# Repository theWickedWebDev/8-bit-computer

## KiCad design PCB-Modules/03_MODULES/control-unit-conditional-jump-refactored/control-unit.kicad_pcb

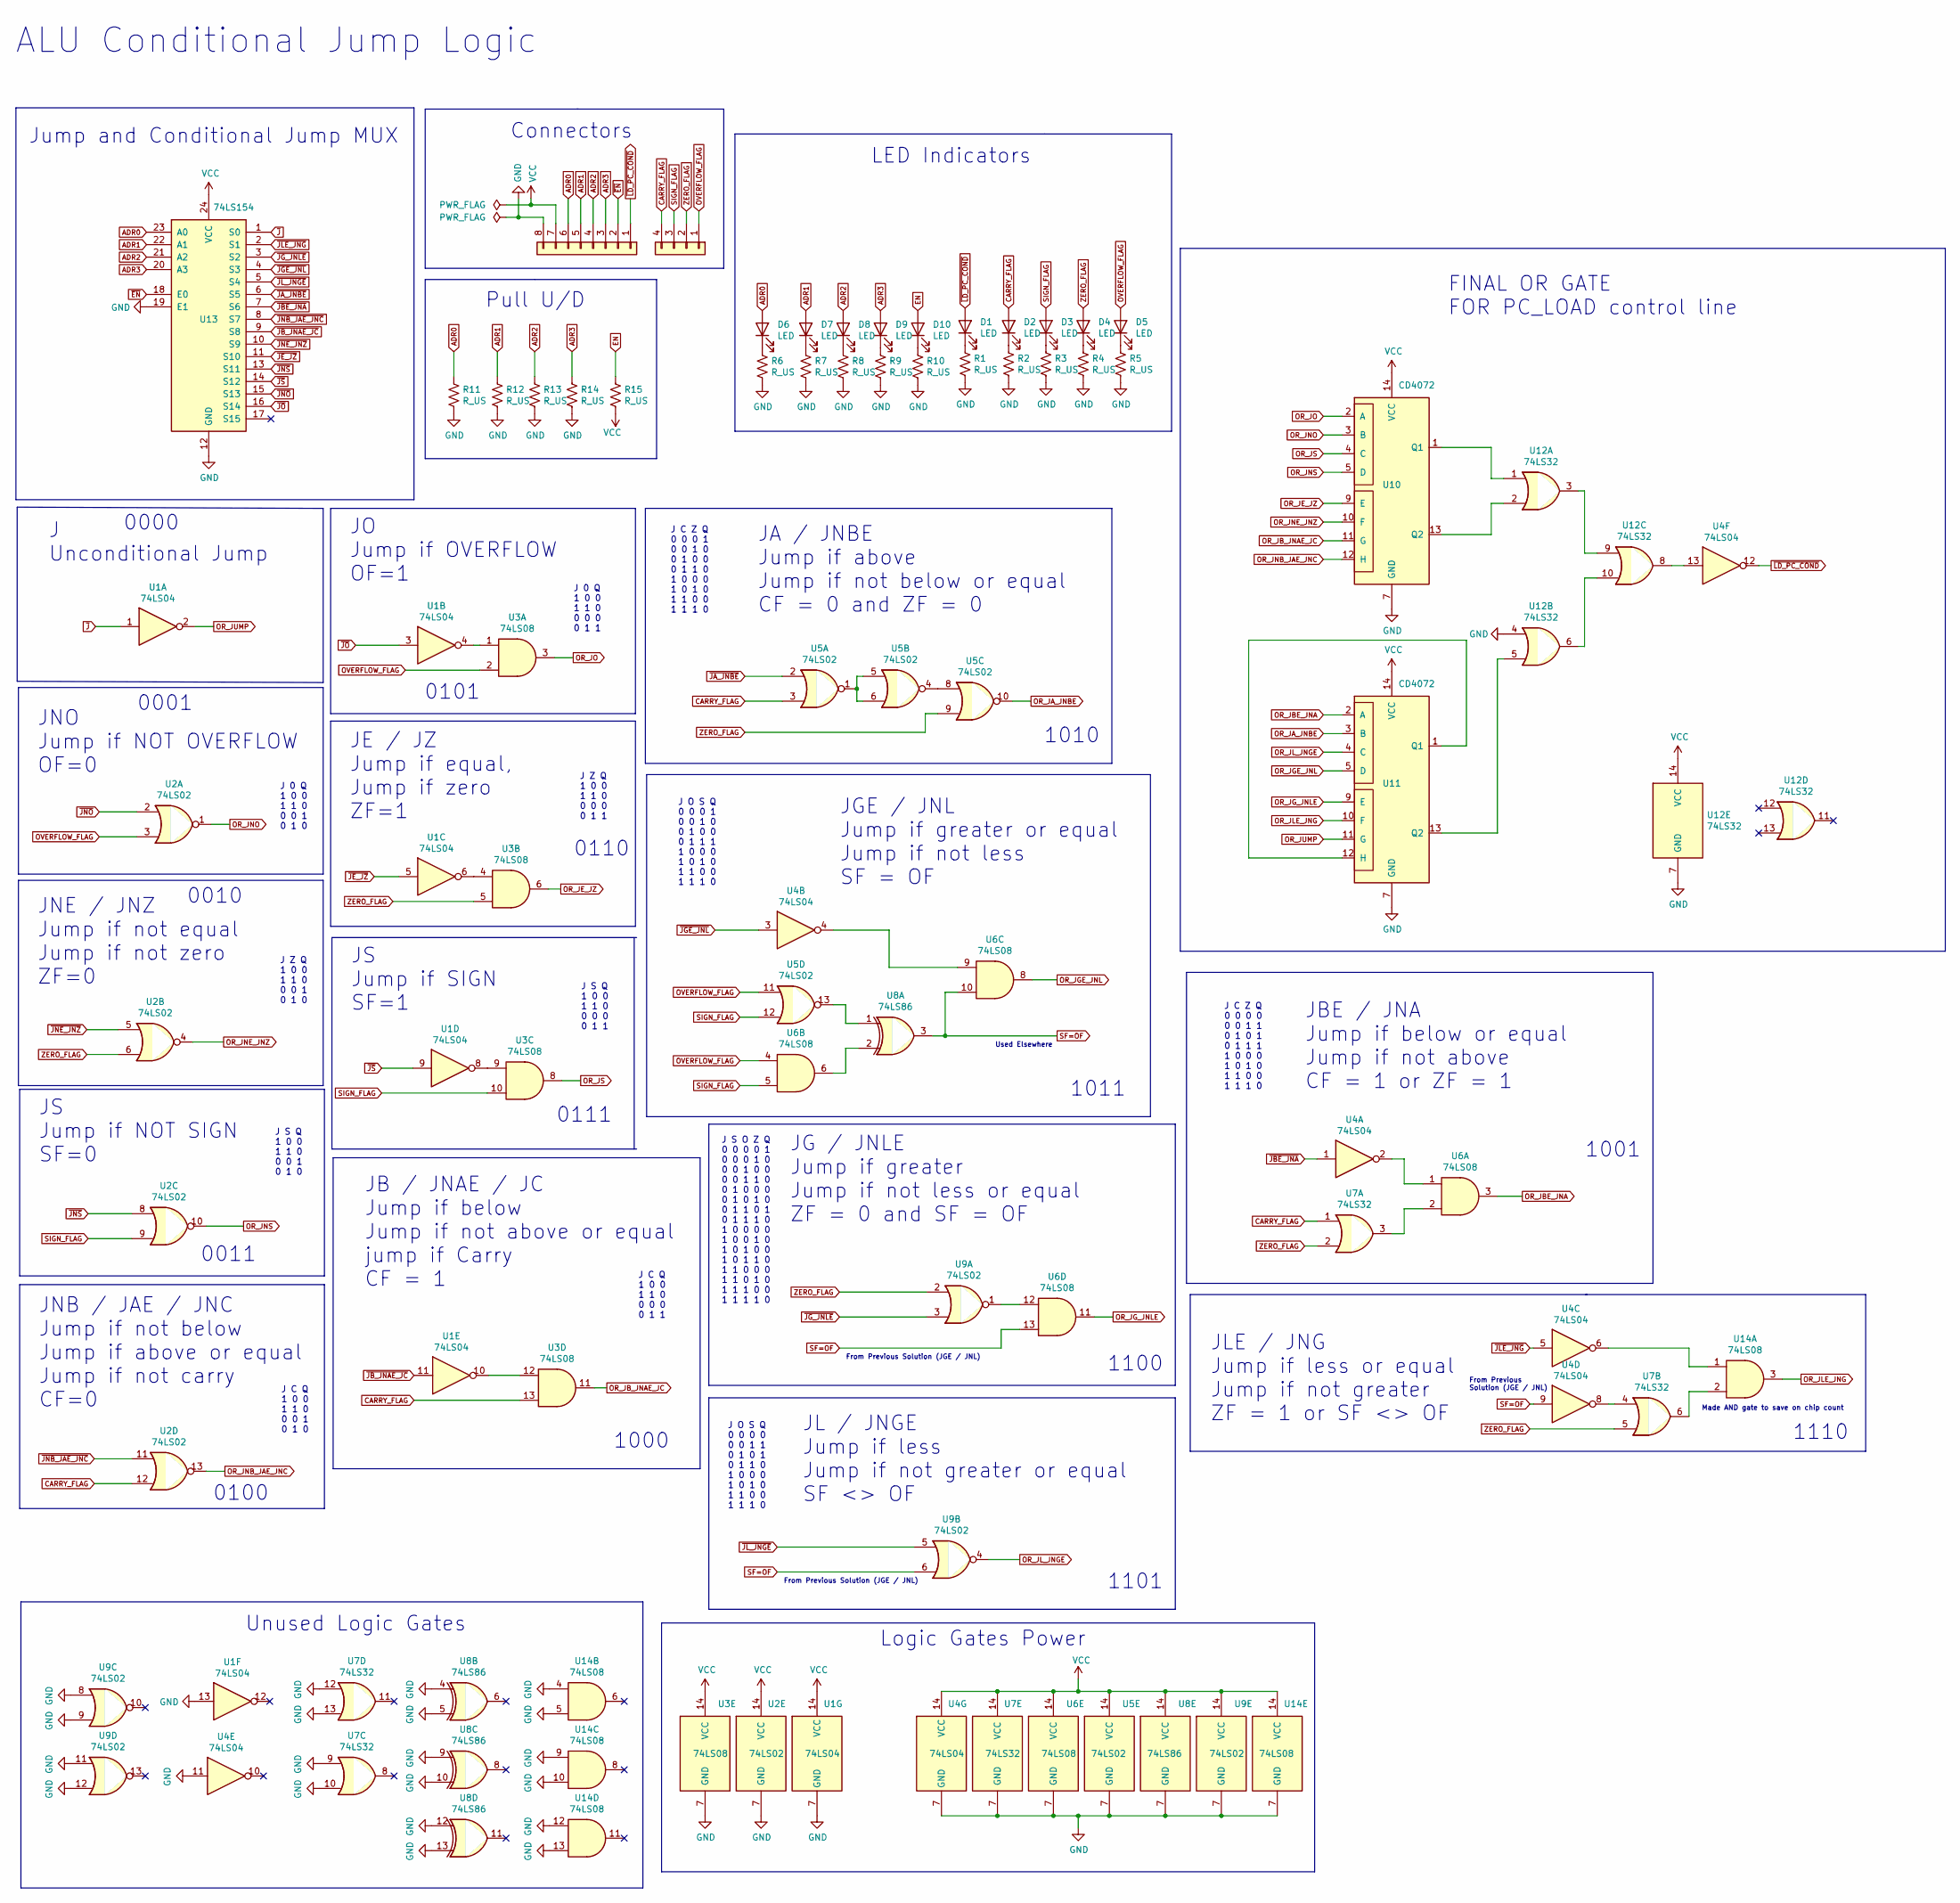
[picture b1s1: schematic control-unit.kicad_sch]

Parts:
D1, D2, D3, D4, D5, D6, D7, D8, D9, D10: LED; LED_0805_2012Metric
J3: Conn_01x08; PinHeader_1x08_P2.54mm_Vertical
J4: Conn_01x04; PinHeader_1x04_P2.54mm_Vertical
R1, R2, R3, R4, R5, R6, R7, R8, R9, R10, R11, R12, R13, R14, R15: R_US; R_0805_2012Metric
U1, U4: 74LS04; TSSOP-14_4.4x5mm_P0.65mm
U2, U5, U9: 74LS02; TSSOP-14_4.4x5mm_P0.65mm
U3, U6, U14: 74LS08; TSSOP-14_4.4x5mm_P0.65mm
U7, U12: 74LS32; TSSOP-14_4.4x5mm_P0.65mm
U8: 74LS86; TSSOP-14_4.4x5mm_P0.65mm
U10, U11: CD4072; SOIC-14_3.9x8.7mm_P1.27mm
U13: 74LS154; SOIC-24W_7.5x15.4mm_P1.27mm

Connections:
ADR0: D6.2 (A), J3.6, R11.1, U13.23 (A0)
ADR1: D7.2 (A), J3.5, R12.1, U13.22 (A1)
ADR2: D8.2 (A), J3.4, R13.1, U13.21 (A2)
ADR3: D9.2 (A), J3.3, R14.1, U13.20 (A3)
CARRY_FLAG: D2.2 (A), J4.4, U2.12, U3.13, U5.3, U7.1
EN: D10.2 (A), R15.1
GND: J3.8, R1.2, R2.2, R3.2, R4.2, R5.2, R6.2, R7.2, R8.2, R9.2, R10.2, R11.2, R12.2, R13.2, R14.2, U1.7 (GND), U1.13, U2.7 (GND), U3.7 (GND), U4.7 (GND), U4.11, U5.7 (GND), U6.7 (GND), U7.7 (GND), U7.9, U7.10, U7.12, U7.13, U8.4, U8.5, U8.7 (GND), U8.9, U8.10, U8.12, U8.13, U9.7 (GND), U9.8, U9.9, U9.11, U9.12, U10.7 (GND), U11.7 (GND), U12.4, U12.7 (GND), U13.12 (GND), U13.19 (E1), U14.4, U14.5, U14.7 (GND), U14.9, U14.10, U14.12, U14.13
unnamed: D1.1 (K), R1.1
unnamed: D2.1 (K), R2.1
unnamed: D3.1 (K), R3.1
unnamed: D4.1 (K), R4.1
unnamed: D5.1 (K), R5.1
unnamed: D6.1 (K), R6.1
unnamed: D7.1 (K), R7.1
unnamed: D8.1 (K), R8.1
unnamed: D9.1 (K), R9.1
unnamed: D10.1 (K), R10.1
unnamed: U1.4, U3.1
unnamed: U1.6, U3.4
unnamed: U1.8, U3.9
unnamed: U1.10, U3.12
unnamed: U4.2, U6.1
unnamed: U4.4, U6.9
unnamed: U4.8, U7.4
unnamed: U5.1, U5.5, U5.6
unnamed: U5.4, U5.8
unnamed: U5.13, U8.1
unnamed: U6.2, U7.3
unnamed: U6.6, U8.2
unnamed: U6.12, U9.1
unnamed: U10.1 (Q1), U12.1
unnamed: U10.13 (Q2), U12.2
unnamed: U11.1 (Q1), U11.12 (H)
unnamed: U11.13 (Q2), U12.5
unnamed: U12.3, U12.9
unnamed: U4.13, U12.8
unnamed: U12.6, U12.10
unnamed: U4.6, U14.1
unnamed: U7.6, U14.2
OR_JA_JNBE: U5.10, U11.3 (B)
OR_JBE_JNA: U6.3, U11.2 (A)
OR_JB_JNAE_JC: U3.11, U10.11 (G)
OR_JE_JZ: U3.6, U10.9 (E)
OR_JGE_JNL: U6.8, U11.5 (D)
OR_JG_JNLE: U6.11, U11.9 (E)
OR_JLE_JNG: U11.10 (F), U14.3
OR_JL_JNGE: U9.4, U11.4 (C)
OR_JNB_JAE_JNC: U2.13, U10.12 (H)
OR_JNE_JNZ: U2.4, U10.10 (F)
OR_JNO: U2.1, U10.3 (B)
OR_JNS: U2.10, U10.5 (D)
OR_JO: U3.3, U10.2 (A)
OR_JS: U3.8, U10.4 (C)
OR_JUMP: U1.2, U11.11 (G)
OVERFLOW_FLAG: D5.2 (A), J4.1, U2.3, U3.2, U5.11, U6.4
SF=OF: U4.9, U6.10, U6.13, U8.3, U9.6
SIGN_FLAG: D3.2 (A), J4.3, U2.9, U3.10, U5.12, U6.5
VCC: J3.7, R15.2, U1.14 (VCC), U2.14 (VCC), U3.14 (VCC), U4.14 (VCC), U5.14 (VCC), U6.14 (VCC), U7.14 (VCC), U8.14 (VCC), U9.14 (VCC), U10.14 (VCC), U11.14 (VCC), U12.14 (VCC), U13.24 (VCC), U14.14 (VCC)
ZERO_FLAG: D4.2 (A), J4.2, U2.6, U3.5, U5.9, U7.2, U7.5, U9.2
~EN: J3.2, U13.18 (E0)
~JA_JNBE: U5.2, U13.6 (S5)
~JBE_JNA: U4.1, U13.7 (S6)
~JB_JNAE_JC: U1.11, U13.9 (S8)
~JE_JZ: U1.5, U13.11 (S10)
~JGE_JNL: U4.3, U13.4 (S3)
~JG_JNLE: U9.3, U13.3 (S2)
~JLE_JNG: U4.5, U13.2 (S1)
~JL_JNGE: U9.5, U13.5 (S4)
~JNB_JAE_JNC: U2.11, U13.8 (S7)
~JNE_JNZ: U2.5, U13.10 (S9)
~JNO: U2.2, U13.15 (S13)
~JNS: U2.8, U13.13 (S11)
~JO: U1.3, U13.16 (S14)
~JS: U1.9, U13.14 (S12)
~J: U1.1, U13.1 (S0)
~LD_PC_COND: D1.2 (A), J3.1, U4.12

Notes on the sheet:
J C Z Q 0 0 0 1 0 0 1 0 0 1 0 0 0 1 1 0 1 0 0 0 1 0 1 0 1 1 0 0 1 1 1 0
JE / JZ Jump if equal, Jump if zero ZF=1
1000
J C Q 1 0 0 1 1 0 0 0 1 0 1 0
0111
0000
Used Elsewhere
J 0 Q 1 0 0 1 1 0 0 0 0 0 1 1
ALU Conditional Jump Logic
JS Jump if NOT SIGN SF=0
J O S Q 0 0 0 1 0 0 1 0 0 1 0 0 0 1 1 1 1 0 0 0 1 0 1 0 1 1 0 0 1 1 1 0
J S Q 1 0 0 1 1 0 0 0 0 0 1 1
From Previous Solution (JGE / JNL)
JA / JNBE Jump if above Jump if not below or equal CF = 0 and ZF = 0
0100
JGE / JNL Jump if greater or equal Jump if not less SF = OF
JLE / JNG Jump if less or equal Jump if not greater ZF = 1 or SF <> OF
From Previous Solution (JGE / JNL)
1100
J O S Q 0 0 0 0 0 0 1 1 0 1 0 1 0 1 1 0 1 0 0 0 1 0 1 0 1 1 0 0 1 1 1 0
0010
J C Z Q 0 0 0 0 0 0 1 1 0 1 0 1 0 1 1 1 1 0 0 0 1 0 1 0 1 1 0 0 1 1 1 0
JS Jump if SIGN SF=1
0001
JB / JNAE / JC Jump if below Jump if not above or equal jump if Carry CF = 1
J S O Z Q 0 0 0 0 1 0 0 0 1 0 0 0 1 0 0 0 0 1 1 0 0 1 0 0 0 0 1 0 1 0 0 1 1 0 1 0 1 1 1 0 1 0 0 0 0 1 0 0 1 0 1 0 1 0 0 1 0 1 1 0 1 1 0 0 0 1 1 0 1 0 1 1 1 0 0 1 1 1 1 0
JNB / JAE / JNC Jump if not below Jump if above or equal Jump if not carry CF=0
Pull U/D
Unused Logic Gates
1101
JNE / JNZ Jump if not equal Jump if not zero ZF=0
JG / JNLE Jump if greater Jump if not less or equal ZF = 0 and SF = OF
JBE / JNA Jump if below or equal Jump if not above CF = 1 or ZF = 1
J Unconditional Jump
J 0 Q 1 0 0 1 1 0 0 0 1 0 1 0
Made AND gate to save on chip count
J C Q 1 0 0 1 1 0 0 0 0 0 1 1
Logic Gates Power
1110
JNO Jump if NOT OVERFLOW OF=0

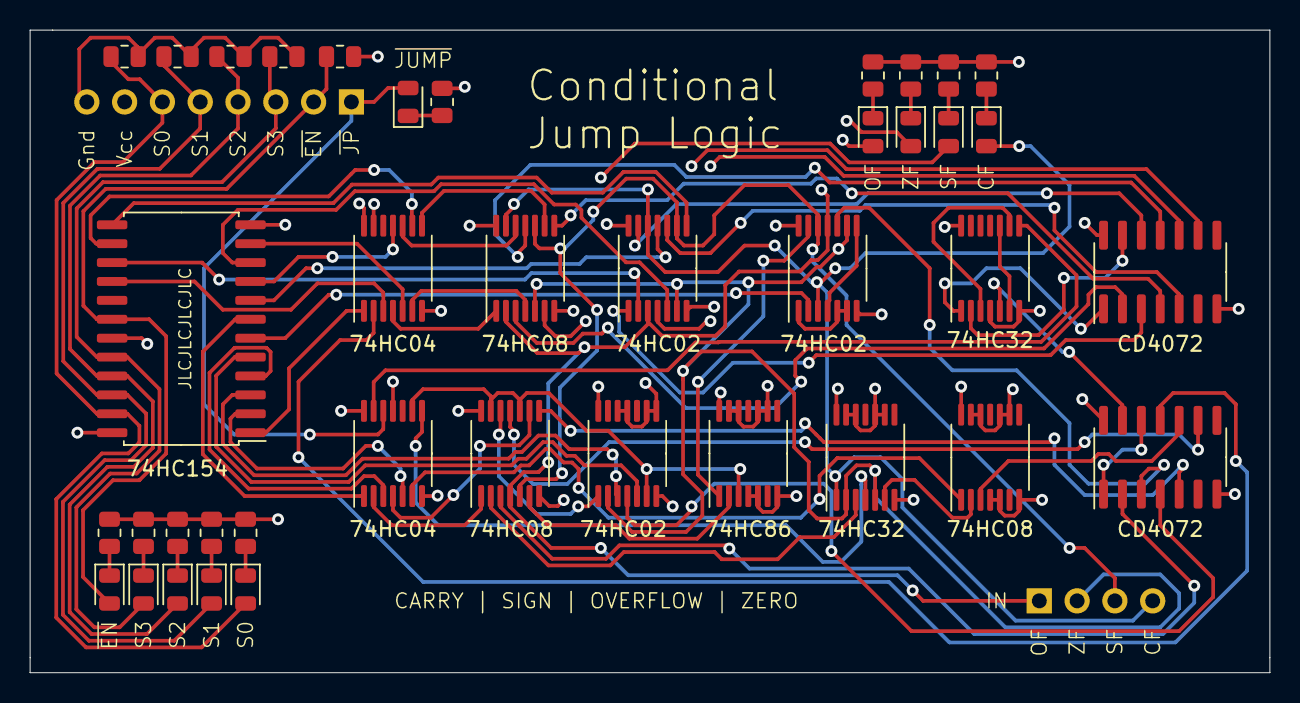
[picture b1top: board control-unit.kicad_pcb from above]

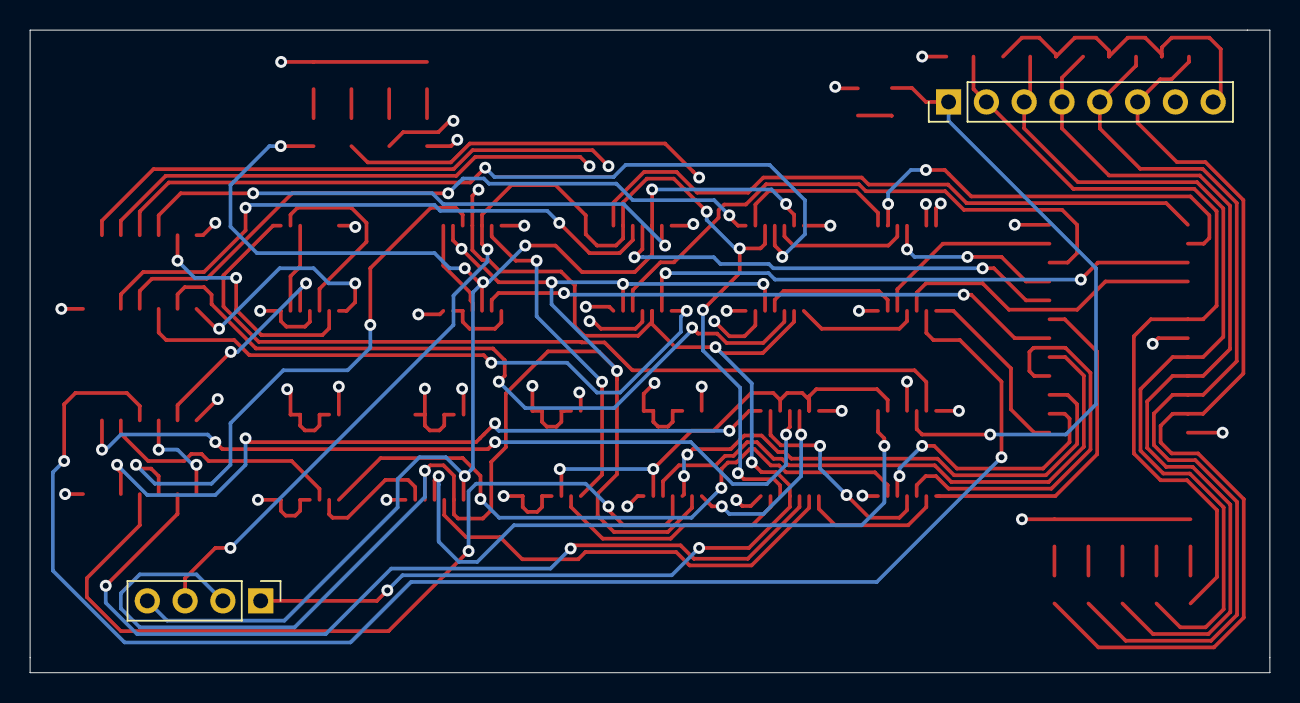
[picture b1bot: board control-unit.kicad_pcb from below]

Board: 4 copper layers, 83.3 x 43.2 mm, 41 parts (2 on the bottom side), 76 nets.

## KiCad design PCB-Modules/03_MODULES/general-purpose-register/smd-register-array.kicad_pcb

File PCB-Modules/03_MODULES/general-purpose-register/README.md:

# General Storage Register

### Status

### Board

### Details

### Control Truth Table

| MS | LS | BS | EN | CP | Mn | Ln | Bn |                                            |
|:--:|:--:|:--:|:--:|:--:|:--:|:--:|:--:|:------------------------------------------:|
|  0 |  0 |  0 |  1 | RE |  x |  x |  x | Latches Data from Main Data BUS            |
|  1 |  1 |  0 |  0 |  x |  x |  x | Qn | Outputs register contents to Main Data BUS |
|  1 |  0 |  1 |  0 |  x |  x | Qn |  x | Outputs register contents to LSB BUS       |
|  0 |  1 |  1 |  0 |  x | Qn |  x |  x | Outputs register contents to MSB BUS       |
|  0 |  0 |  0 |  0 |  x | Qn | Qn | Qn | Outputs register to all BUS's              |

`BS` - (Active Low) Output to Main Data BUS

`MS` - (Active Low) Output to MSB BUS

`MS` - (Active Low) Output to LSB BUS

`EN` - Enable load on register. Latches on the rising edge of the clock

`CP` - Clock Pulse

`M[0..7]` - BUS output for MSB

`L[0..7]` - BUS output for LSB

`B[0..7]` - BUS output for Main Data Bus

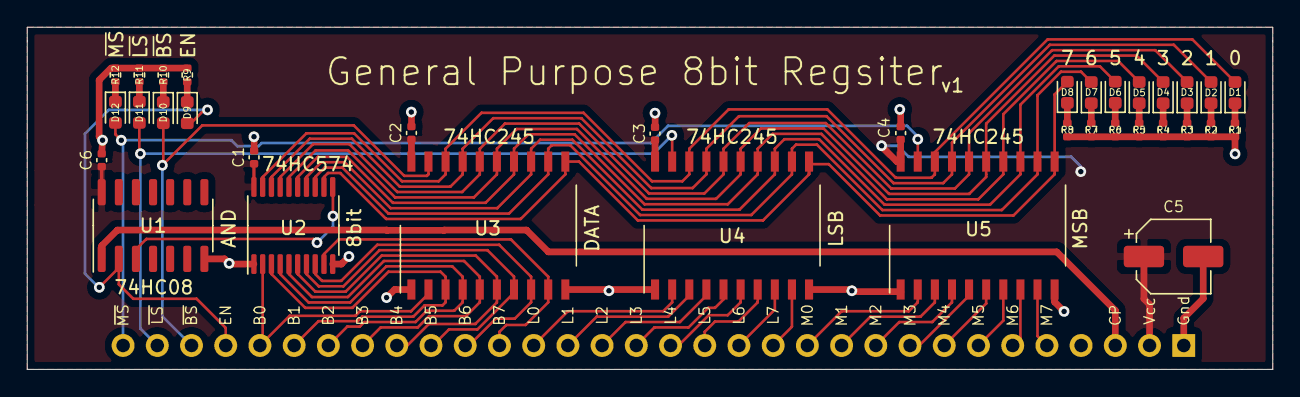
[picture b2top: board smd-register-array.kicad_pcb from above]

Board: 2 copper layers, 92.5 x 25.4 mm, 36 parts (1 on the bottom side), 52 nets.

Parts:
C1, C2, C3, C4, C6: CL05A106MQ5NUNC; C_0402_1005Metric
C5: SMD-ECAP-5x5.8; CP_Elec_5x5.8
D1, D2, D3, D4, D5, D6, D7, D8: 19-217/GHC-YR1S2/3T; LED_0603_1608Metric
D9, D10, D11, D12: 19-217/BHC-ZL1M2RY/3T; LED_0603_1608Metric
J1: Conn_01x32; PinHeader_1x32_P2.54mm_Vertical
R1, R2, R3, R4, R5, R6, R7, R8, R9, R10, R11, R12: 0402WGF1001TCE; R_0402_1005Metric
U1: 74HC08D,653; SOIC-14_3.9x8.7mm_P1.27mm
U2: 74HC574PW,118; TSSOP-20_4.4x6.5mm_P0.65mm
U3, U4, U5: 74HC245D,653; SO-20_12.8x7.5mm_P1.27mm

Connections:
/BUS_OUT: D10.2, J1.30, U3.19
/EN: D9.2, J1.29, U1.2
/LSB_OUT: D11.2, J1.31, U4.19
/MSB_OUT: D12.2, J1.32, U5.19
A0: D1.2, U2.19, U3.18, U4.18, U5.18
A1: D2.2, U2.18, U3.17, U4.17, U5.17
A2: D3.2, U2.17, U3.16, U4.16, U5.16
A3: D4.2, U2.16, U3.15, U4.15, U5.15
A4: D5.2, U2.15, U3.14, U4.14, U5.14
A5: D6.2, U2.14, U3.13, U4.13, U5.13
A6: D7.2, U2.13, U3.12, U4.12, U5.12
A7: D8.2, U2.12, U3.11, U4.11, U5.11
BUS_00: J1.28, U2.2, U3.2
BUS_01: J1.27, U2.3, U3.3
BUS_02: J1.26, U2.4, U3.4
BUS_03: J1.25, U2.5, U3.5
BUS_04: J1.24, U2.6, U3.6
BUS_05: J1.23, U2.7, U3.7
BUS_06: J1.22, U2.8, U3.8
BUS_07: J1.21, U2.9, U3.9
CLOCK: J1.3, U1.1
GND: C1.2, C2.2, C3.2, C4.2, C5.2, C6.2, J1.1, R1.2, R2.2, R3.2, R4.2, R5.2, R6.2, R7.2, R8.2, R9.2, R10.2, R11.2, R12.2, U1.7, U2.1, U2.10, U3.1, U3.10, U4.1, U4.10, U5.1, U5.10
LSB_00: J1.20, U4.2
LSB_01: J1.19, U4.3
LSB_02: J1.18, U4.4
LSB_03: J1.17, U4.5
LSB_04: J1.16, U4.6
LSB_05: J1.15, U4.7
LSB_06: J1.14, U4.8
LSB_07: J1.13, U4.9
MSB_00: J1.12, U5.2
MSB_01: J1.11, U5.3
MSB_02: J1.10, U5.4
MSB_03: J1.9, U5.5
MSB_04: J1.8, U5.6
MSB_05: J1.7, U5.7
MSB_06: J1.6, U5.8
MSB_07: J1.5, U5.9
unnamed: D1.1, R1.1
unnamed: D2.1, R2.1
unnamed: D3.1, R3.1
unnamed: D4.1, R4.1
unnamed: D5.1, R5.1
unnamed: D6.1, R6.1
unnamed: D7.1, R7.1
unnamed: D8.1, R8.1
unnamed: D9.1, R9.1
unnamed: D10.1, R10.1
unnamed: D11.1, R11.1
unnamed: D12.1, R12.1
unnamed: U1.3, U2.11
VCC: C1.1, C2.1, C3.1, C4.1, C5.1, C6.1, J1.2, U1.14, U2.20, U3.20, U4.20, U5.20

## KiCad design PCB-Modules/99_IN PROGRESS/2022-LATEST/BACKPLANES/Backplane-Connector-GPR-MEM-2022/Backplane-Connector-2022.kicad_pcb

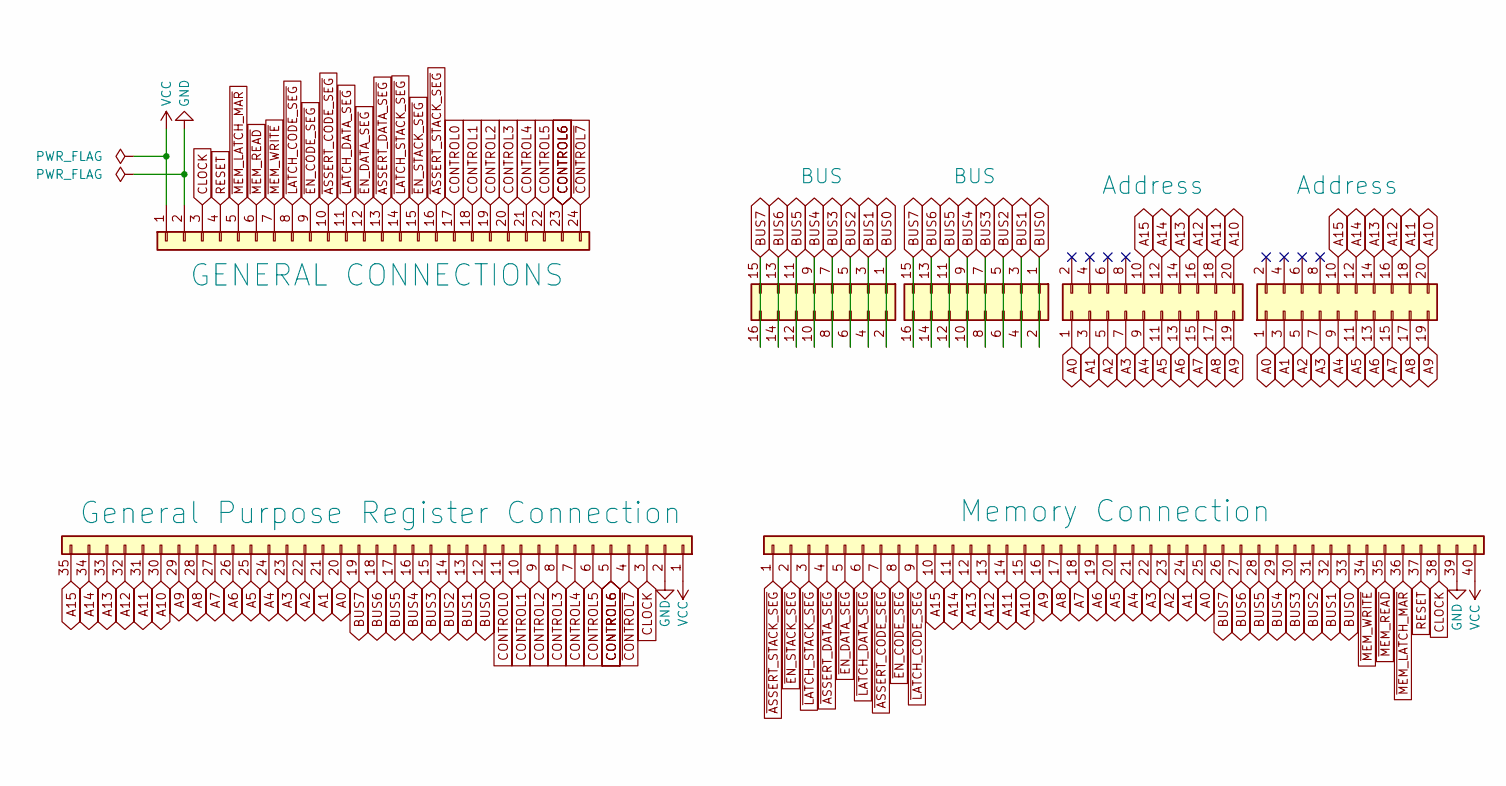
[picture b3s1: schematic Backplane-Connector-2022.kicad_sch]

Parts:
J1: Conn_01x24; PinSocket_1x24_P2.54mm_Horizontal
J2: Conn_01x35; PinSocket_1x35_P2.54mm_Horizontal
J3, J4: Conn_01x08; PinHeader_2x08_P2.54mm_Vertical
J5: Conn_01x40; PinSocket_1x40_P2.54mm_Horizontal
J6, J7: Conn_02x20_Odd_Even; IDC-Header_2x10_P2.54mm_Vertical

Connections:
A0: J2.20, J5.25, J6.1, J7.1
A1: J2.21, J5.24, J6.3, J7.3
A2: J2.22, J5.23, J6.5, J7.5
A3: J2.23, J5.22, J6.7, J7.7
A4: J2.24, J5.21, J6.9, J7.9
A5: J2.25, J5.20, J6.11, J7.11
A6: J2.26, J5.19, J6.13, J7.13
A7: J2.27, J5.18, J6.15, J7.15
A8: J2.28, J5.17, J6.17, J7.17
A9: J2.29, J5.16, J6.19, J7.19
A10: J2.30, J5.15, J6.20, J7.20
A11: J2.31, J5.14, J6.18, J7.18
A12: J2.32, J5.13, J6.16, J7.16
A13: J2.33, J5.12, J6.14, J7.14
A14: J2.34, J5.11, J6.12, J7.12
A15: J2.35, J5.10, J6.10, J7.10
BUS0: J2.12, J3.1, J3.2, J4.1, J4.2, J5.33
BUS1: J2.13, J3.3, J3.4, J4.3, J4.4, J5.32
BUS2: J2.14, J3.5, J3.6, J4.5, J4.6, J5.31
BUS3: J2.15, J3.7, J3.8, J4.7, J4.8, J5.30
BUS4: J2.16, J3.9, J3.10, J4.9, J4.10, J5.29
BUS5: J2.17, J3.11, J3.12, J4.11, J4.12, J5.28
BUS6: J2.18, J3.13, J3.14, J4.13, J4.14, J5.27
BUS7: J2.19, J3.15, J3.16, J4.15, J4.16, J5.26
CLOCK: J1.3, J2.3, J5.38
CONTROL0: J1.17, J2.11
CONTROL1: J1.18, J2.10
CONTROL2: J1.19, J2.9
CONTROL3: J1.20, J2.8
CONTROL4: J1.21, J2.7
CONTROL5: J1.22, J2.6
CONTROL6: J1.23, J2.5
GND: J1.2, J2.2, J5.39
RESET: J1.4, J5.37
VCC: J1.1, J2.1, J5.40
~ASSERT_CODE_SEG: J1.10, J5.7
~ASSERT_DATA_SEG: J1.13, J5.4
~ASSERT_STACK_SEG: J1.16, J5.1
~CONTROL7: J1.24, J2.4
~EN_CODE_SEG: J1.9, J5.8
~EN_DATA_SEG: J1.12, J5.5
~EN_STACK_SEG: J1.15, J5.2
~LATCH_CODE_SEG: J1.8, J5.9
~LATCH_DATA_SEG: J1.11, J5.6
~LATCH_STACK_SEG: J1.14, J5.3
~MEM_LATCH_MAR: J1.5, J5.36
~MEM_READ: J1.6, J5.35
~MEM_WRITE: J1.7, J5.34

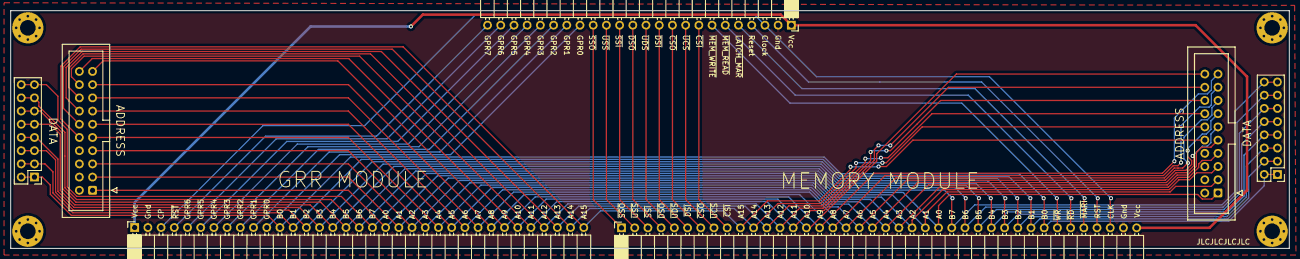
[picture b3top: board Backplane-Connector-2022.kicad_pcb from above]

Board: 2 copper layers, 245.9 x 45.7 mm, 7 parts (0 on the bottom side), 48 nets.

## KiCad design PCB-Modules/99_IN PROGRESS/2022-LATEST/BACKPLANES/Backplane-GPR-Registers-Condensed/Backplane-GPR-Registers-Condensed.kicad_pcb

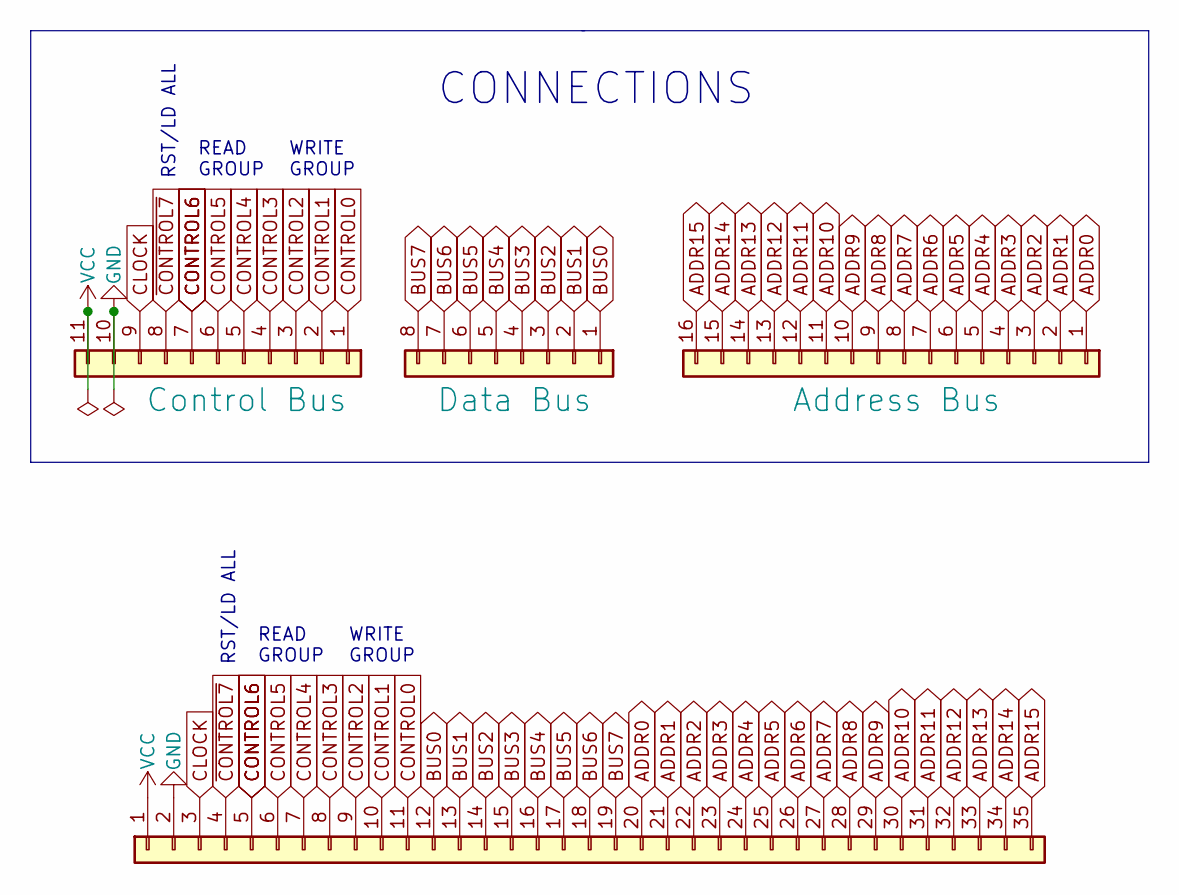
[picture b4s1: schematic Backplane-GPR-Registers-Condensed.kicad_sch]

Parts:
J1: Conn_01x08; PinSocket_1x11_P2.54mm_Vertical
J2: Conn_01x16; PinSocket_1x08_P2.54mm_Vertical
J3: Conn_01x35; PinHeader_1x35_P2.54mm_Horizontal
J4: Conn_01x11; PinSocket_1x16_P2.54mm_Vertical

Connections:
ADDR0: J3.20, J4.1
ADDR1: J3.21, J4.2
ADDR2: J3.22, J4.3
ADDR3: J3.23, J4.4
ADDR4: J3.24, J4.5
ADDR5: J3.25, J4.6
ADDR6: J3.26, J4.7
ADDR7: J3.27, J4.8
ADDR8: J3.28, J4.9
ADDR9: J3.29, J4.10
ADDR10: J3.30, J4.11
ADDR11: J3.31, J4.12
ADDR12: J3.32, J4.13
ADDR13: J3.33, J4.14
ADDR14: J3.34, J4.15
ADDR15: J3.35, J4.16
BUS0: J2.1, J3.12
BUS1: J2.2, J3.13
BUS2: J2.3, J3.14
BUS3: J2.4, J3.15
BUS4: J2.5, J3.16
BUS5: J2.6, J3.17
BUS6: J2.7, J3.18
BUS7: J2.8, J3.19
CLOCK: J1.9, J3.3
CONTROL0: J1.1, J3.11
CONTROL1: J1.2, J3.10
CONTROL2: J1.3, J3.9
CONTROL3: J1.4, J3.8
CONTROL4: J1.5, J3.7
CONTROL5: J1.6, J3.6
CONTROL6: J1.7, J3.5
GND: J1.10, J3.2
VCC: J1.11, J3.1
~CONTROL7: J1.8, J3.4

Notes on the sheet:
WRITE GROUP
CONNECTIONS
READ GROUP
RST/LD ALL

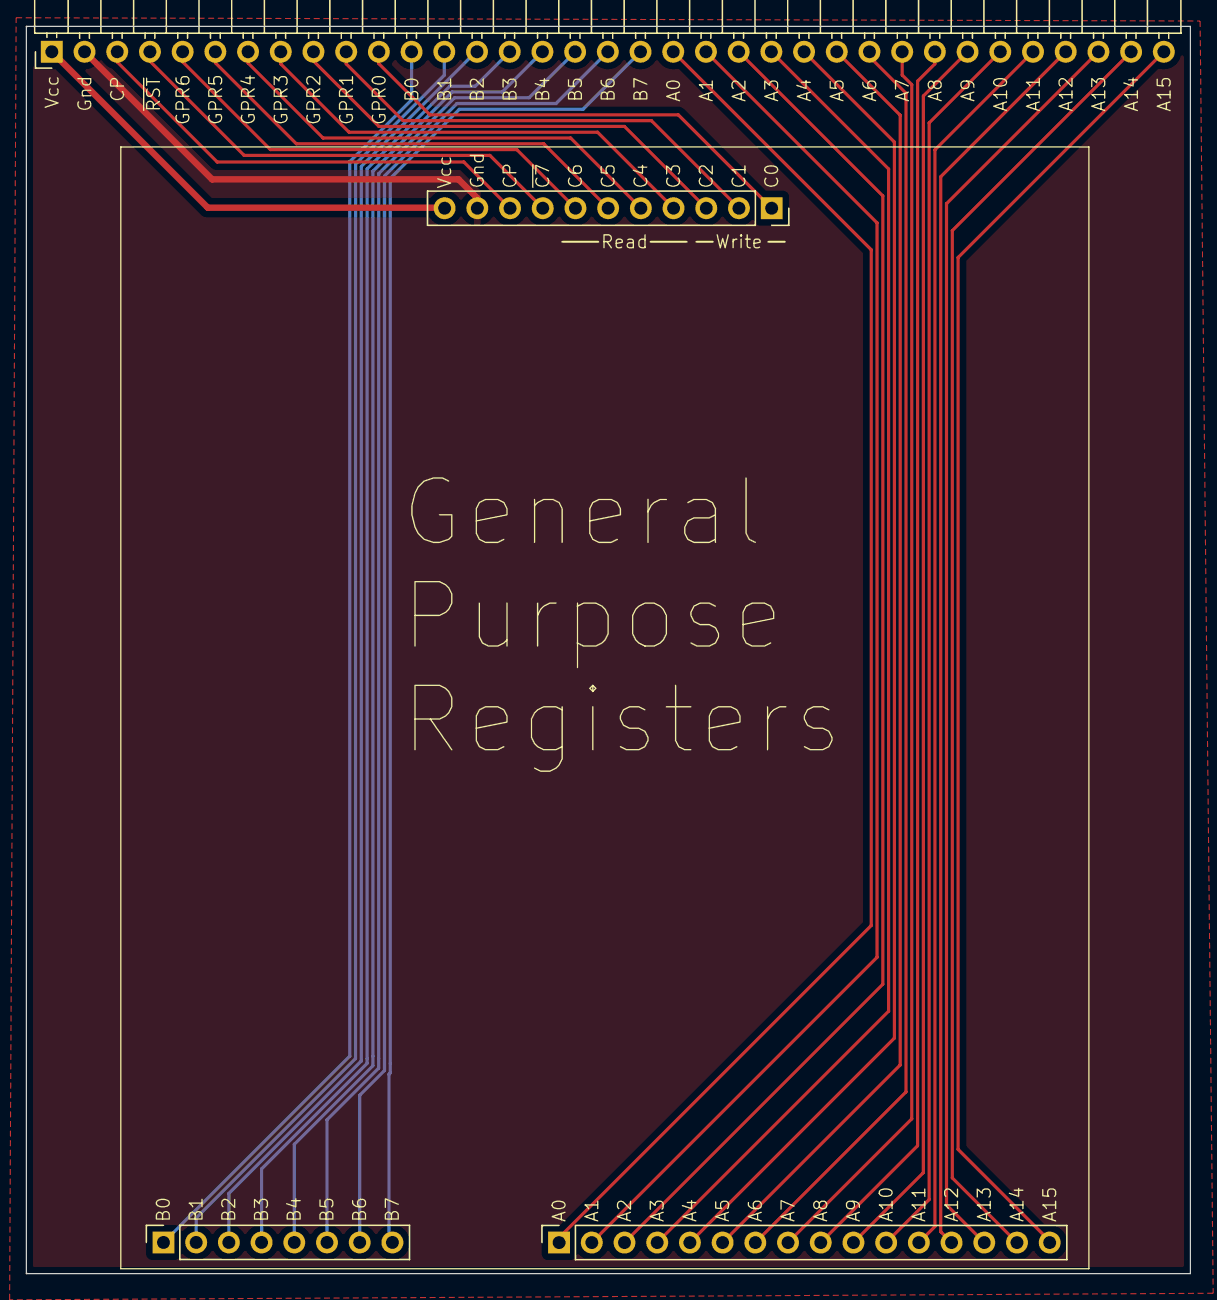
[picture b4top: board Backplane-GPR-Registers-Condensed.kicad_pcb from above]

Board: 2 copper layers, 90.4 x 96.9 mm, 4 parts (0 on the bottom side), 35 nets.

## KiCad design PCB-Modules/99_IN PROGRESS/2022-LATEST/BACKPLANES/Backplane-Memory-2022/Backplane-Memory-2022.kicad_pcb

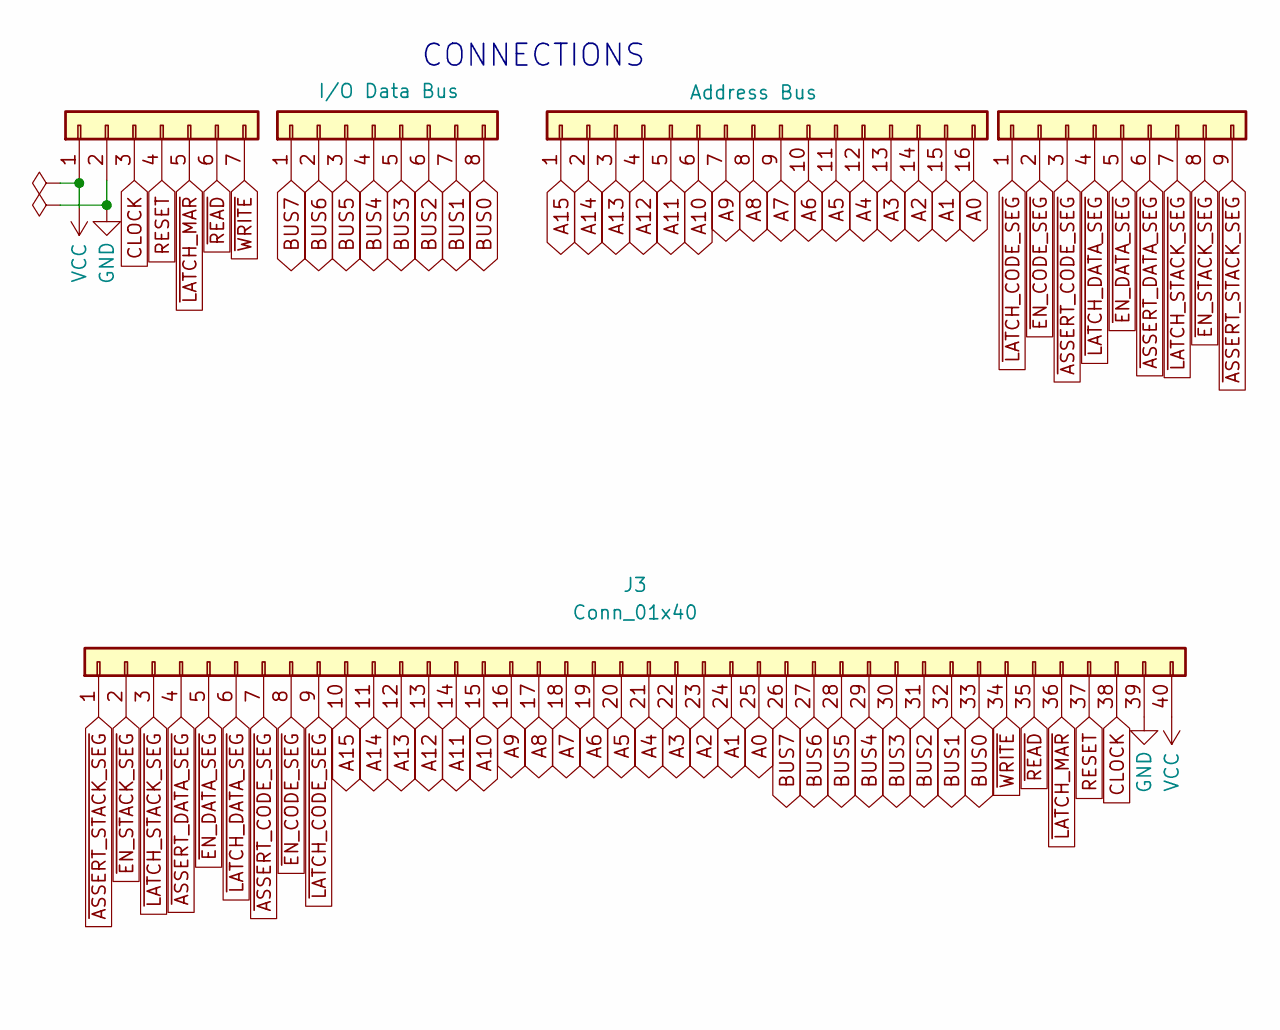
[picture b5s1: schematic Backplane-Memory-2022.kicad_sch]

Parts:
J1: Conn_01x07; PinSocket_1x07_P2.54mm_Vertical
J2: Conn_01x08; PinSocket_1x08_P2.54mm_Vertical
J3: Conn_01x40; PinHeader_1x40_P2.54mm_Horizontal
J4: Conn_01x16; PinSocket_1x16_P2.54mm_Vertical
J5: Conn_01x09; PinSocket_1x09_P2.54mm_Vertical

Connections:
A0: J3.25, J4.16
A1: J3.24, J4.15
A2: J3.23, J4.14
A3: J3.22, J4.13
A4: J3.21, J4.12
A5: J3.20, J4.11
A6: J3.19, J4.10
A7: J3.18, J4.9
A8: J3.17, J4.8
A9: J3.16, J4.7
A10: J3.15, J4.6
A11: J3.14, J4.5
A12: J3.13, J4.4
A13: J3.12, J4.3
A14: J3.11, J4.2
A15: J3.10, J4.1
BUS0: J2.8, J3.33
BUS1: J2.7, J3.32
BUS2: J2.6, J3.31
BUS3: J2.5, J3.30
BUS4: J2.4, J3.29
BUS5: J2.3, J3.28
BUS6: J2.2, J3.27
BUS7: J2.1, J3.26
CLOCK: J1.3, J3.38
GND: J1.2, J3.39
RESET: J1.4, J3.37
VCC: J1.1, J3.40
~ASSERT_CODE_SEG: J3.7, J5.3
~ASSERT_DATA_SEG: J3.4, J5.6
~ASSERT_STACK_SEG: J3.1, J5.9
~EN_CODE_SEG: J3.8, J5.2
~EN_DATA_SEG: J3.5, J5.5
~EN_STACK_SEG: J3.2, J5.8
~LATCH_CODE_SEG: J3.9, J5.1
~LATCH_DATA_SEG: J3.6, J5.4
~LATCH_MAR: J1.5, J3.36
~LATCH_STACK_SEG: J3.3, J5.7
~READ: J1.6, J3.35
~WRITE: J1.7, J3.34

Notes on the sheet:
CONNECTIONS

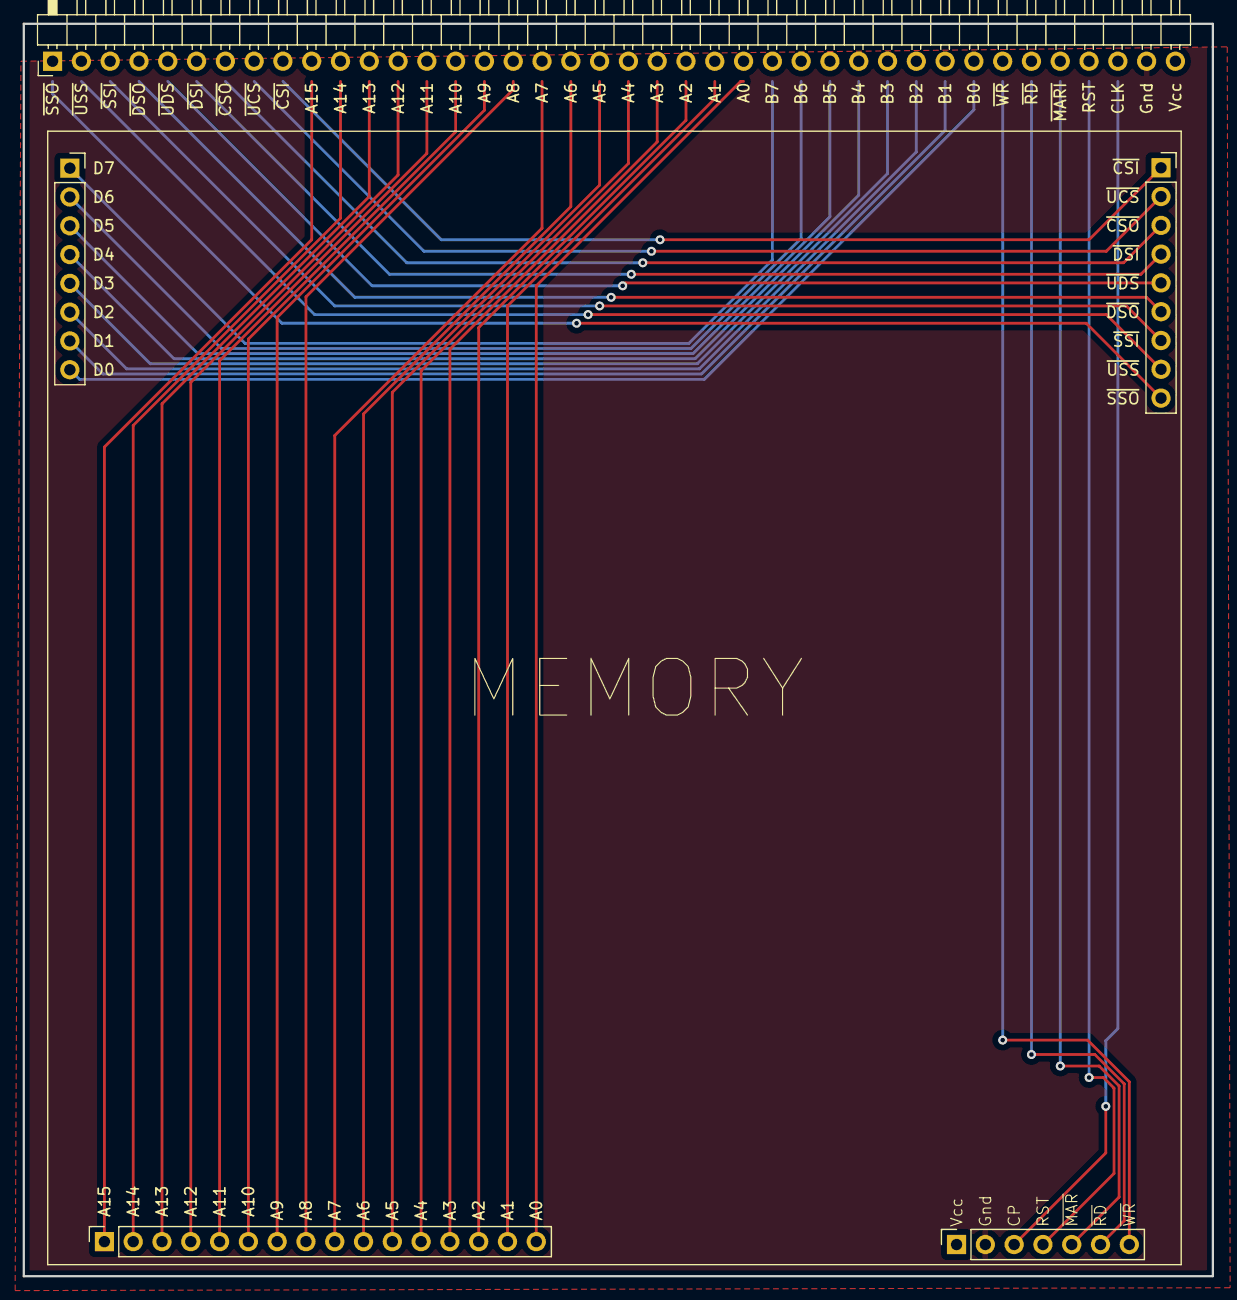
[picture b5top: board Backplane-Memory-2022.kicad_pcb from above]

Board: 2 copper layers, 104.9 x 110.5 mm, 5 parts (0 on the bottom side), 40 nets.
